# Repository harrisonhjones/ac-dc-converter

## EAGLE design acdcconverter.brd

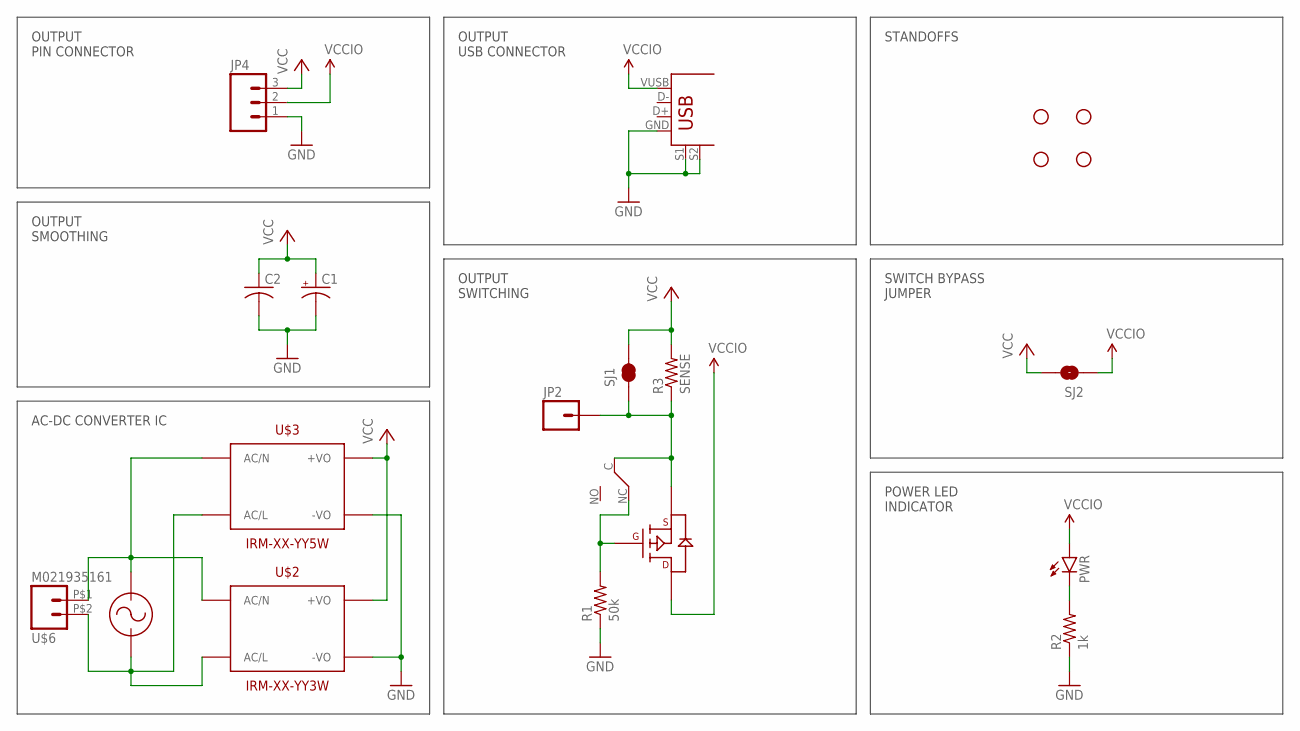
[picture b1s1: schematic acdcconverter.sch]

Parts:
C1: CPOL-USE2-5; E2-5
C2: C-USC0603; C0603
JP2: M01PTH; 1X01
JP4: M03PTH; 1X03
PWR: LED0603; LED-0603
R1: 50k; R0603
R2: 1k; R0603
R3: SENSE; 0805
SJ1: JUMPER-PAD-2-NC_BY_TRACE; PAD-JUMPER-2-NC_BY_TRACE_YES_SILK
SJ2: SOLDERJUMPERNO; SJ_2S-NO
STANDOFF1, STANDOFF2, STANDOFF3, STANDOFF4: STAND-OFF
U$1: AC-CONNECTOR770W-X2; 770W-X2
U$2: IRM-XX-YY3W; IRM-03-YY
U$3: IRM-XX-YY5W; IRM-05-YY
U$5: SWITCH-SPDT; SWITCH-1825232-1
U$6: M021935161; M02-1935161
U$7: USB-FEMALE; FOXCONN-113N-USB-A-FEMALE
U$8: MOSFET-PDMG2305UX; SOT23-3

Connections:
AC/L: U$1.P$1 (AC1), U$2.AC/L, U$3.AC/L, U$6.P$2 (2)
AC/N: U$1.P$2 (AC2), U$2.AC/N, U$3.AC/N, U$6.P$1 (1)
GND: C1.-, C2.2, JP4.1, R1.1, R2.1, U$2.-VO, U$3.-VO, U$7.GND, U$7.S1, U$7.S2
unnamed: R1.2, U$5.NC, U$8.3 (GATE)
unnamed: JP2.1, R3.1, SJ1.1, U$5.C, U$8.1 (SOURCE)
unnamed: PWR.C, R2.2
VCC: C1.+, C2.1, JP4.3, R3.2, SJ1.2, SJ2.2, U$2.+VO, U$3.+VO
VCCIO: JP4.2, PWR.A, SJ2.1, U$7.VUSB, U$8.2 (DRAIN)

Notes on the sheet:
AC-DC CONVERTER IC
OUTPUT SMOOTHING
OUTPUT PIN CONNECTOR
OUTPUT USB CONNECTOR
OUTPUT SWITCHING
STANDOFFS
POWER LED INDICATOR
SWITCH BYPASS JUMPER

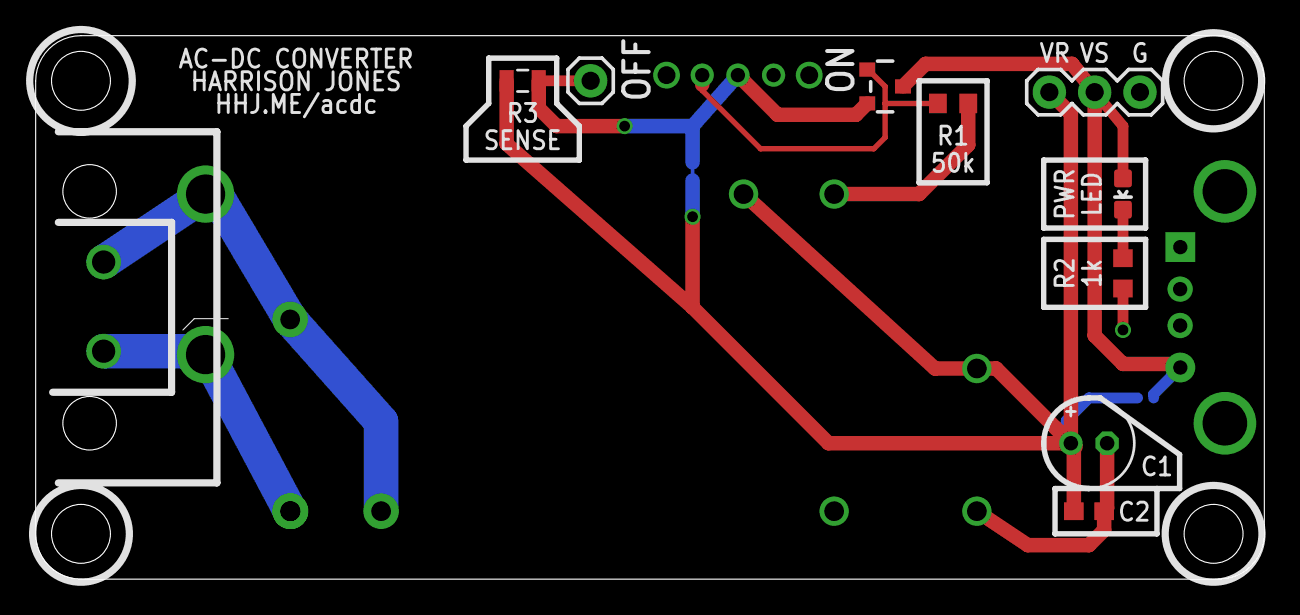
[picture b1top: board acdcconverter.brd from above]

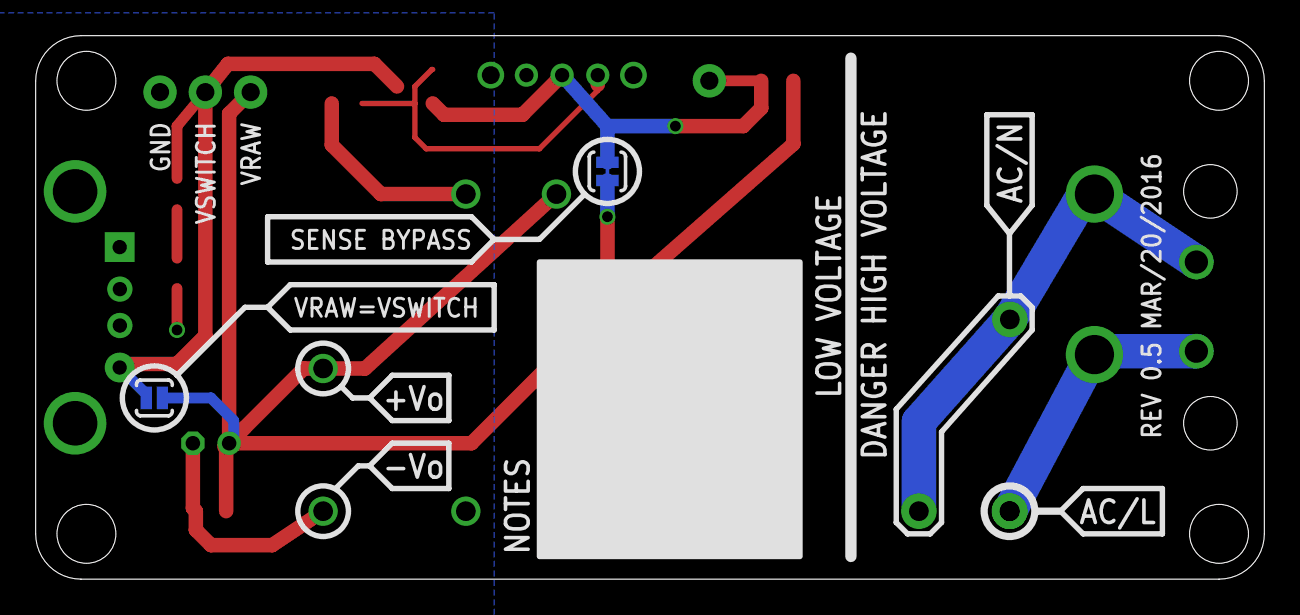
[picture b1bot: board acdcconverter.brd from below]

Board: 2 copper layers, 68.9 x 30.5 mm, 21 parts (2 on the bottom side), 8 nets.

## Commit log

2016-03-20 Cleaned up the schematic's layout
2016-03-20 Added PDFs for schematic and board
2016-03-20 Fixed mosfet switch circuit
2016-03-20 Updated MOSFET again
2016-03-20 Rounded the corners
2016-03-21 Removed wattage label and enlarged notes label
2016-03-21 Updated revision and added shortlink

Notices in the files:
parts and their libraries:
SparkFun-LED: Licensing: Creative Commons ShareAlike 4.0 International - https://creativecommons.org/licenses/by-sa/4.0
